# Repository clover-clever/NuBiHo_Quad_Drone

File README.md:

2025, first semester Microprocessor Quad Drone Project

Based on Arduino Uno R3 for control with PPM Signal

PPM for SPRacing R3

Self-made PCBs
  - 6V Regulator does not work well,(Burnt)(delete 6V Switching Regulator and use it)
  - LM1117 - 12V --> 5V(too big voltage difference, do not use for high load, or just do not use it)

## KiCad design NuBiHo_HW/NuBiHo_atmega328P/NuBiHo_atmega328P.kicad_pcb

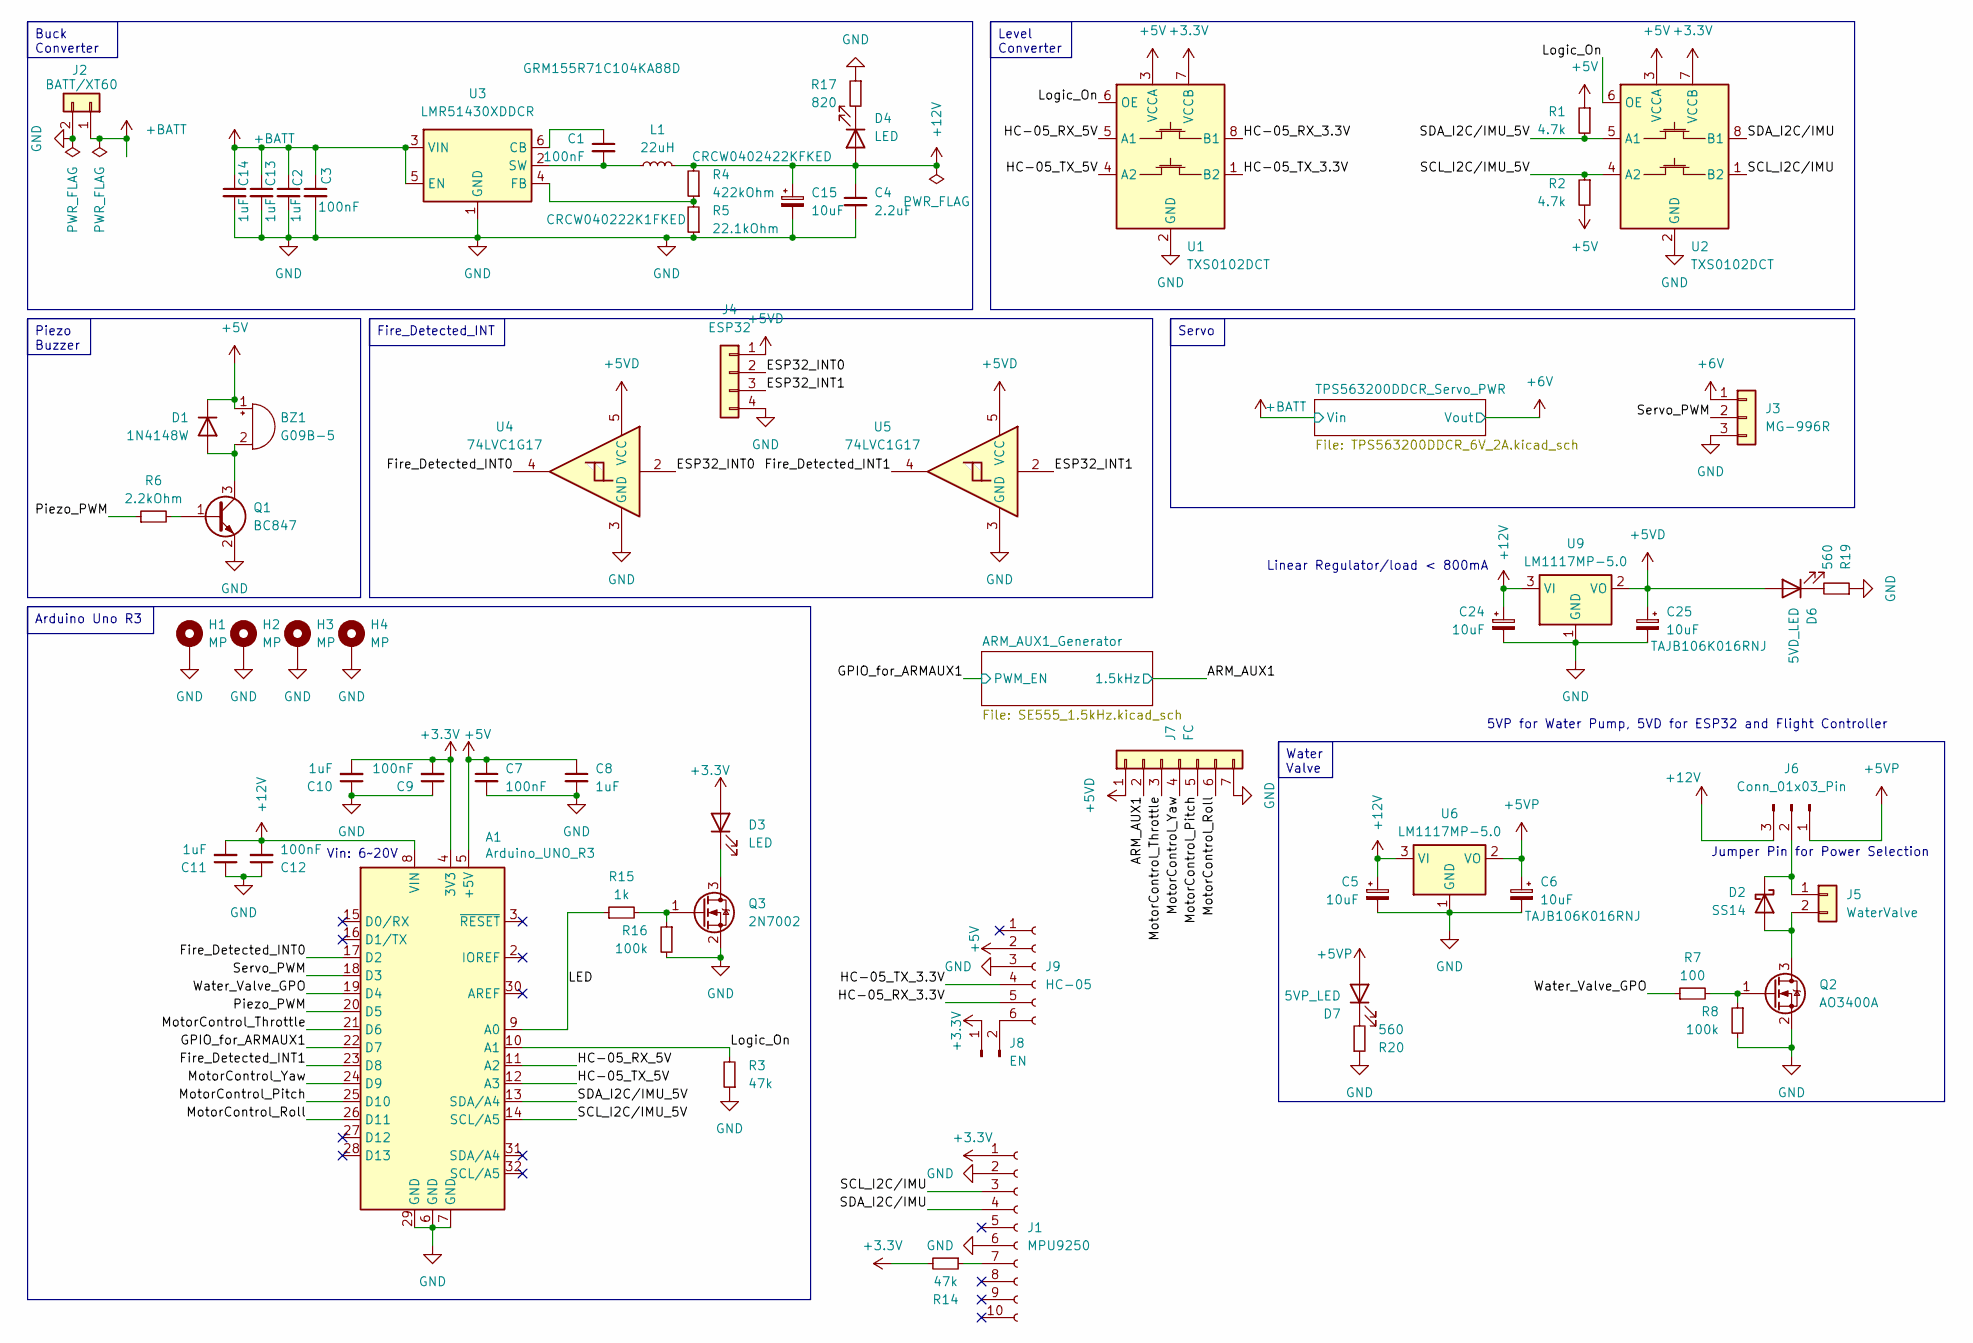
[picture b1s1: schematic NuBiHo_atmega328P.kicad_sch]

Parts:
A1: Arduino_UNO_R3
BZ1: G09B-5; [GEC] G09B-5
C1: 100nF; C_0402_1005Metric; Part No. GRM155R71C104KA88D
C2, C13, C14: 1uF; C_0603_1608Metric; Part No. GRM188R71E105KA12D
C3: 100nF; C_0805_2012Metric; Part No. GRM21BR71H104KA01L
C4: 2.2uF; C_0805_2012Metric; Part No. GRM21BR71C225KA12L
C5: 10uF; CP_EIA-3528-21_Kemet-B_Pad1.50x2.35mm_HandSolder
C6: 10uF; CP_EIA-3528-21_Kemet-B_Pad1.50x2.35mm_HandSolder; Part No. TAJB106K016RNJ
C7, C9, C12: 100nF; C_0402_1005Metric
C8, C10, C11: 1uF; C_0402_1005Metric
C15: 10uF; CP_EIA-6032-28_Kemet-C; Part No. 593D106X9025C2TE3
C24: 10uF; CP_EIA-3528-21_Kemet-B
C25: 10uF; CP_EIA-3528-21_Kemet-B; Part No. TAJB106K016RNJ
D1: 1N4148W; D_SOD-123
D2: SS14; D_SMA
D3, D4: LED; LED_0805_2012Metric
D6: 5VD_LED; LED_0805_2012Metric
D7: 5VP_LED; LED_0805_2012Metric
H1, H2, H3, H4: MP; MountingHole_3.2mm_M3_Pad_Via
J1: MPU9250; PinHeader_1x10_P2.54mm_Vertical
J2: BATT/XT60; AMASS_XT60-M_1x02_P7.20mm_Vertical
J3: MG-996R; Molex_SPOX_5267-03A_1x03_P2.50mm_Vertical
J4: ESP32; Molex_SPOX_5267-04A_1x04_P2.50mm_Vertical
J5: WaterValve; Molex_SPOX_5267-02A_1x02_P2.50mm_Vertical
J6: Conn_01x03_Pin; PinHeader_1x03_P2.54mm_Vertical
J7: FC; Molex_SPOX_5267-07A_1x07_P2.50mm_Vertical
J8: EN; PinHeader_1x02_P2.54mm_Vertical
J9: HC-05; PinHeader_1x06_P2.54mm_Vertical
L1: 22uH; INDPM172172X700N; Part No. IHLP6767GZER220M11
Q1: BC847; SOT-23
Q2: AO3400A; SOT-23
Q3: 2N7002; SOT-23
R1, R2: 4.7k; R_0402_1005Metric
R3, R14: 47k; R_0402_1005Metric
R4: 422kOhm; R_0603_1608Metric; Part No. CRCW0402422KFKED
R5: 22.1kOhm; R_0603_1608Metric; Part No. CRCW040222K1FKED
R6: 2.2kOhm; R_0402_1005Metric
R7: 100; R_0402_1005Metric
R8, R16: 100k; R_0402_1005Metric
R15: 1k; R_0402_1005Metric
R17: 820; R_0402_1005Metric
R19, R20: 560; R_0402_1005Metric
U1, U2: TXS0102DCT; SSOP-8_2.95x2.8mm_P0.65mm
U3: LMR51430XDDCR; SOT-23-6
U4, U5: 74LVC1G17; SOT-23-5
U6, U9: LM1117MP-5.0; SOT-223-3_TabPin2

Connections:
+3.3V: A1.4 (3V3), C9.2, C10.2, D3.2 (A), J1.1, J8.1, R14.2, U1.7 (VCCB), U2.7 (VCCB)
+5V: A1.5 (+5V), BZ1.1 (+), C7.1, C8.1, D1.1 (K), J9.2, R1.1, R2.2, U1.3 (VCCA), U2.3 (VCCA); also elsewhere on the board
+5VD: C25.1, D6.2 (A), J4.1, J7.1, U4.5 (VCC), U5.5 (VCC), U9.2 (VO)
+5VP: C6.1, D7.2 (A), J6.1, U6.2 (VO)
+6V: J3.1; also elsewhere on the board
+12V: A1.8 (VIN), C4.1, C5.1, C11.2, C12.2, C15.1, C24.1, D4.2 (A), J6.3, L1.2, R4.2, U6.3 (VI), U9.3 (VI)
+BATT: C2.1, C3.1, C13.1, C14.1, J2.1, U3.3 (VIN), U3.5 (EN); also elsewhere on the board
/ARM_AUX1: J7.2; also elsewhere on the board
/ESP32_INT0: J4.2, U4.2
/ESP32_INT1: J4.3, U5.2
/Fire_Detected_INT0: A1.17 (D2), U4.4
/Fire_Detected_INT1: A1.23 (D8), U5.4
/GPIO_for_ARMAUX1: A1.22 (D7); also elsewhere on the board
/HC-05_RX_3.3V: J9.5, U1.8 (B1)
/HC-05_RX_5V: A1.11 (A2), U1.5 (A1)
/HC-05_TX_3.3V: J9.4, U1.1 (B2)
/HC-05_TX_5V: A1.12 (A3), U1.4 (A2)
/LED: A1.9 (A0), R15.1
/Logic_On: A1.10 (A1), R3.2, U1.6 (OE), U2.6 (OE)
/MotorControl_Pitch: A1.25 (D10), J7.5
/MotorControl_Roll: A1.26 (D11), J7.6
/MotorControl_Throttle: A1.21 (D6), J7.3
/MotorControl_Yaw: A1.24 (D9), J7.4
/Piezo_PWM: A1.20 (D5), R6.1
/SCL_I2C/IMU: J1.3, U2.1 (B2)
/SCL_I2C/IMU_5V: A1.14 (SCL/A5), R2.1, U2.4 (A2)
/SDA_I2C/IMU: J1.4, U2.8 (B1)
/SDA_I2C/IMU_5V: A1.13 (SDA/A4), R1.2, U2.5 (A1)
/Servo_PWM: A1.18 (D3), J3.2
/Water_Valve_GPO: A1.19 (D4), R7.1
GND: A1.6 (GND), A1.7 (GND), A1.29 (GND), C2.2, C3.2, C4.2, C5.2, C6.2, C7.2, C8.2, C9.1, C10.1, C11.1, C12.1, C13.2, C14.2, C15.2, C24.2, C25.2, H1.1, H2.1, H3.1, H4.1, J1.2, J1.6, J2.2, J3.3, J4.4, J7.7, J9.3, Q1.2 (E), Q2.2 (S), Q3.2 (S), R3.1, R5.1, R8.2, R16.2, R17.1, R19.1, R20.1, U1.2 (GND), U2.2 (GND), U3.1 (GND), U4.3 (GND), U5.3 (GND), U6.1 (GND), U9.1 (GND); also elsewhere on the board
unnamed: BZ1.2 (-), D1.2 (A), Q1.3 (C)
unnamed: D2.2 (A), J5.2, Q2.3 (D)
unnamed: D2.1 (K), J5.1, J6.2
unnamed: D3.1 (K), Q3.3 (D)
unnamed: D4.1 (K), R17.2
unnamed: D6.1 (K), R19.2
unnamed: D7.1 (K), R20.2
unnamed: J1.7, R14.1
unnamed: J8.2, J9.6
unnamed: Q1.1 (B), R6.2
unnamed: Q2.1 (G), R7.2, R8.1
unnamed: Q3.1 (G), R15.2, R16.1
unnamed: C1.1, U3.6 (CB)
unnamed: R4.1, R5.2, U3.4 (FB)
unnamed: C1.2, L1.1, U3.2 (SW)

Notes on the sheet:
Vin: 6~20V
5VP for Water Pump, 5VD for ESP32 and Flight Controller
Linear Regulator/load < 800mA
Jumper Pin for Power Selection
Servo
Piezo Buzzer
Level Converter
Fire_Detected_INT
Arduino Uno R3
Water Valve
Buck Converter

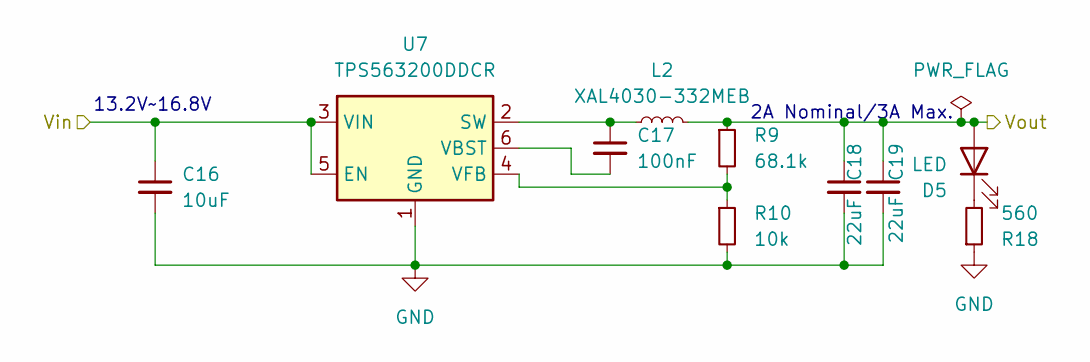
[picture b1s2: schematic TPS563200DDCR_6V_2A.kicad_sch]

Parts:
C16: 10uF; C_1206_3216Metric; Part No. GRM31CR61E106KA12L
C17: 100nF; C_0805_2012Metric; Part No. CC0805KRX7R9BB104
C18: 22uF; C_1206_3216Metric; Part No. GRM31CR71A226KE15L
C19: 22uF; C_1206_3216Metric
D5: LED; LED_0805_2012Metric
L2: XAL4030-332MEB; L_Coilcraft_XAL4030-XXX
R9: 68.1k; R_0603_1608Metric; Part No. RC0402FR-0768K1L
R10: 10k; R_0603_1608Metric; Part No. CRCW040210K0FKED
R18: 560; R_0402_1005Metric
U7: TPS563200DDCR; SOT-23-6

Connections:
+6V: C18.1, C19.1, D5.2 (A), L2.2, R9.1; also elsewhere on the board
+BATT: C16.1, U7.3 (VIN), U7.5 (EN); also elsewhere on the board
GND: C16.2, C18.2, C19.2, R10.2, R18.1, U7.1 (GND); also elsewhere on the board
unnamed: D5.1 (K), R18.2
unnamed: C17.1, L2.1, U7.2 (SW)
unnamed: C17.2, U7.6 (VBST)
unnamed: R9.2, R10.1, U7.4 (VFB)

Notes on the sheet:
2A Nominal/3A Max.
13.2V~16.8V

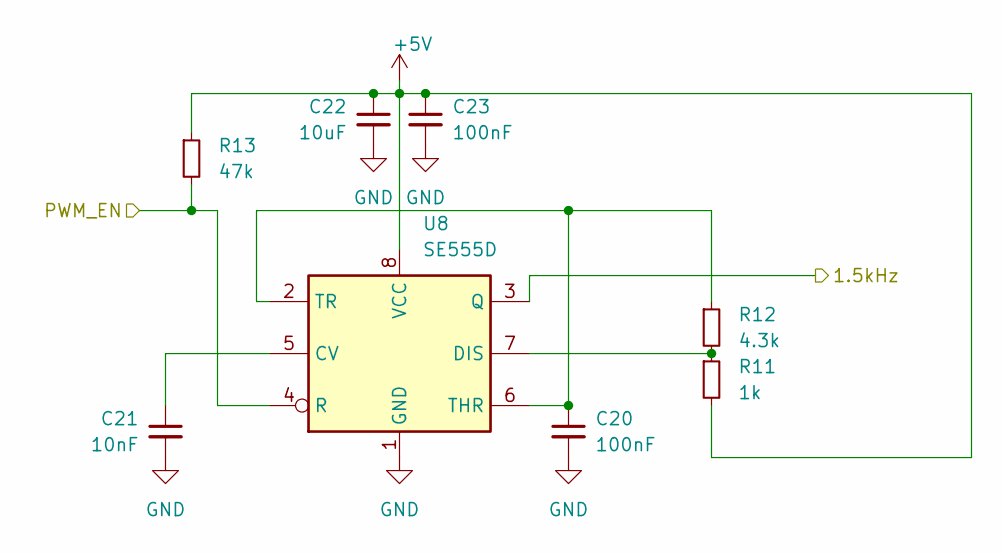
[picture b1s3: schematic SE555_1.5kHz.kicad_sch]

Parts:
C20: 100nF; C_1206_3216Metric
C21: 10nF; C_0603_1608Metric
C22: 10uF; C_0402_1005Metric
C23: 100nF; C_0402_1005Metric
R11: 1k; R_0402_1005Metric
R12: 4.3k; R_0402_1005Metric
R13: 47k; R_0402_1005Metric
U8: SE555D; SOIC-8_3.9x4.9mm_P1.27mm

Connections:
+5V: C22.1, C23.1, R11.2, R13.1, U8.8 (VCC); also elsewhere on the board
/ARM_AUX1: U8.3 (Q); also elsewhere on the board
/GPIO_for_ARMAUX1: R13.2, U8.4 (R); also elsewhere on the board
GND: C20.2, C21.2, C22.2, C23.2, U8.1 (GND); also elsewhere on the board
unnamed: C21.1, U8.5 (CV)
unnamed: R11.1, R12.2, U8.7 (DIS)
unnamed: C20.1, R12.1, U8.2 (TR), U8.6 (THR)

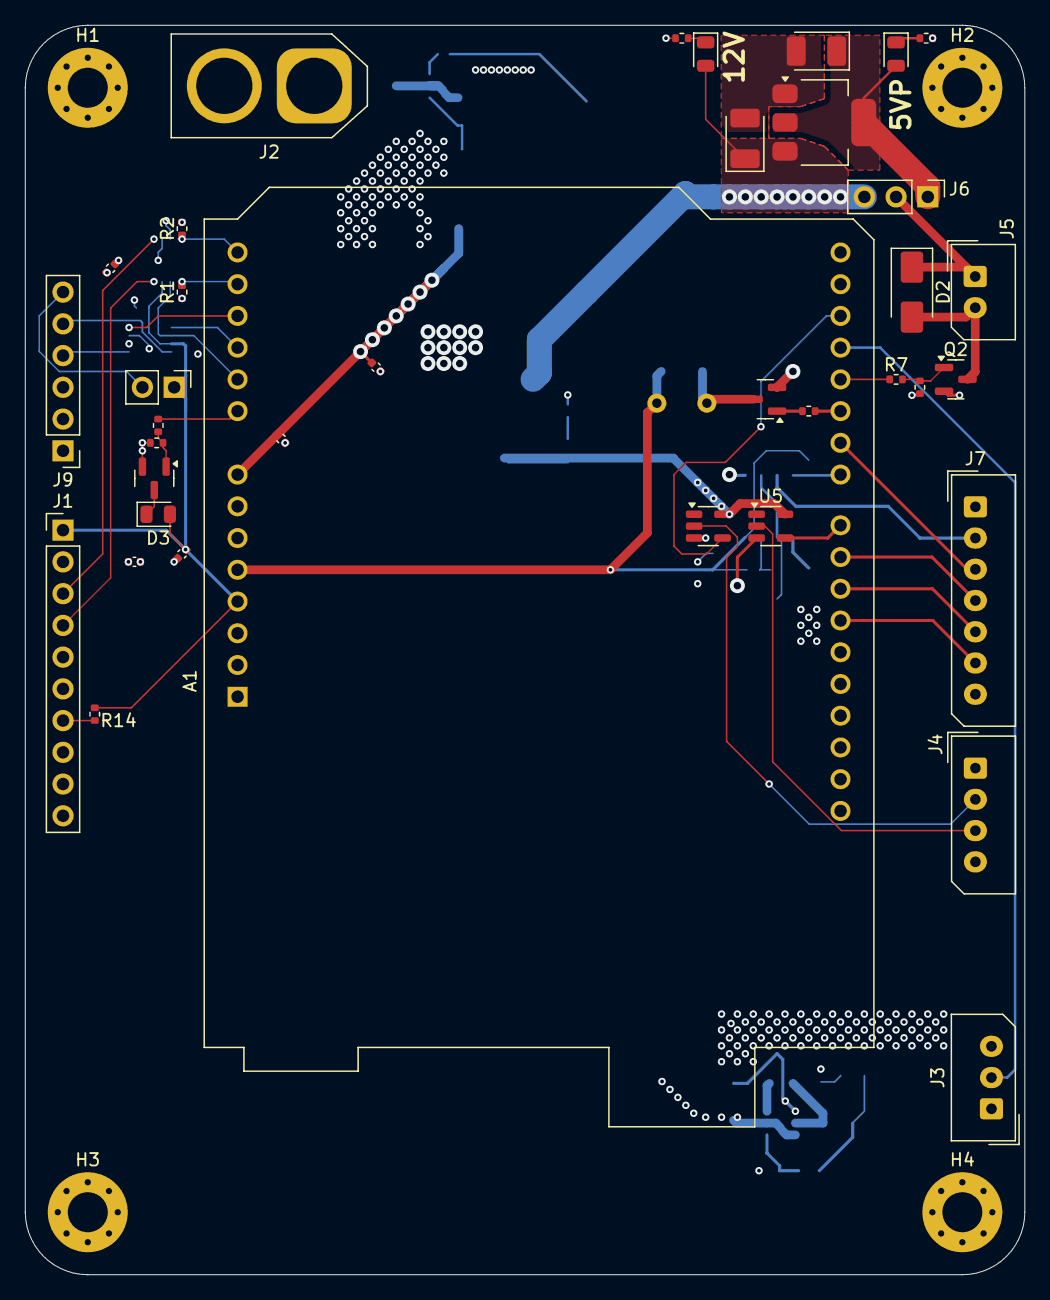
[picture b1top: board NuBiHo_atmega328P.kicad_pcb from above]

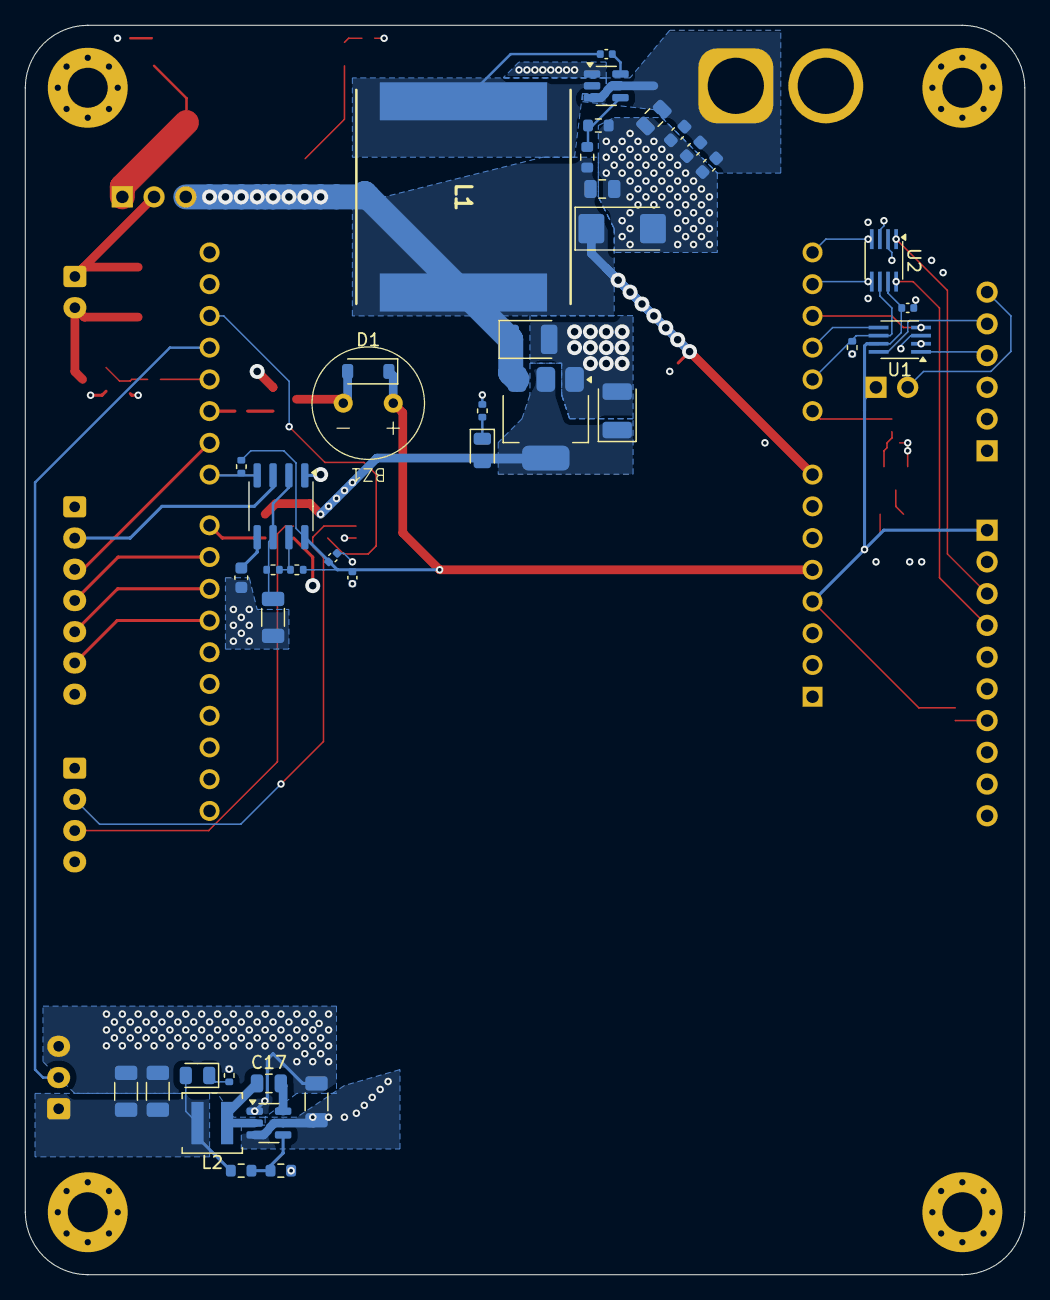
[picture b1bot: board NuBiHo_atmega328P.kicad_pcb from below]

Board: 4 copper layers, 80.0 x 100.0 mm, 81 parts (40 on the bottom side), 53 nets.

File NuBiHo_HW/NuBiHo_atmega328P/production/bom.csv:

Designator,Footprint,Quantity,Value,LCSC Part #
A1,Arduino_UNO_R3,1,Arduino_UNO_R3,
BZ1,[GEC] G09B-5,1,G09B-5,
"C1, C12, C23, C7, C9",0402,5,100nF,
"C10, C11, C8",0402,3,1uF,
"C13, C14, C2",0603,3,1uF,
C15,CP_EIA-6032-28_Kemet-C,1,10uF,
C16,1206,1,10uF,
"C17, C3",0805,2,100nF,
"C18, C19",1206,2,22uF,
C20,1206,1,100nF,
C21,0603,1,10nF,
C22,0402,1,10uF,
"C24, C25",CP_EIA-3528-21_Kemet-B,2,10uF,
C4,0805,1,2.2uF,
"C5, C6",CP_EIA-3528-21_Kemet-B_Pad1.50x2.35mm_HandSolder,2,10uF,
D1,D_SOD-123,1,1N4148W,
D2,D_SMA,1,SS14,
"D3, D4, D5",0805,3,LED,
D6,0805,1,5VD_LED,
D7,0805,1,5VP_LED,
J1,PinHeader_1x10_P2.54mm_Vertical,1,MPU9250,
J2,AMASS_XT60-M_1x02_P7.20mm_Vertical,1,BATT/XT60,
J3,Molex_SPOX_5267-03A_1x03_P2.50mm_Vertical,1,MG-996R,
J4,Molex_SPOX_5267-04A_1x04_P2.50mm_Vertical,1,ESP32,
J5,Molex_SPOX_5267-02A_1x02_P2.50mm_Vertical,1,WaterValve,
J6,PinHeader_1x03_P2.54mm_Vertical,1,Conn_01x03_Pin,
J7,Molex_SPOX_5267-07A_1x07_P2.50mm_Vertical,1,FC,
J8,PinHeader_1x02_P2.54mm_Vertical,1,EN,
J9,PinHeader_1x06_P2.54mm_Vertical,1,HC-05,
L1,INDPM172172X700N,1,22uH,
L2,L_Coilcraft_XAL4030-XXX,1,XAL4030-332MEB,
Q1,SOT-23,1,BC847,
Q2,SOT-23,1,AO3400A,
Q3,SOT-23,1,2N7002,
"R1, R2",0402,2,4.7k,
R10,0603,1,10k,
"R11, R15",0402,2,1k,
R12,0402,1,4.3k,
"R13, R14, R3",0402,3,47k,
"R16, R8",0402,2,100k,
R17,0402,1,820,
"R18, R19, R20",0402,3,560,
R4,0603,1,422kOhm,
R5,0603,1,22.1kOhm,
R6,0402,1,2.2kOhm,
R7,0402,1,100,
R9,0603,1,68.1k,
"U1, U2",SSOP-8_2.95x2.8mm_P0.65mm,2,TXS0102DCT,
U3,SOT-23-6,1,LMR51430XDDCR,
"U4, U5",SOT-23-5,2,74LVC1G17,
"U6, U9",SOT-223-3_TabPin2,2,LM1117MP-5.0,
U7,SOT-23-6,1,TPS563200DDCR,
U8,SOIC-8_3.9x4.9mm_P1.27mm,1,SE555D,

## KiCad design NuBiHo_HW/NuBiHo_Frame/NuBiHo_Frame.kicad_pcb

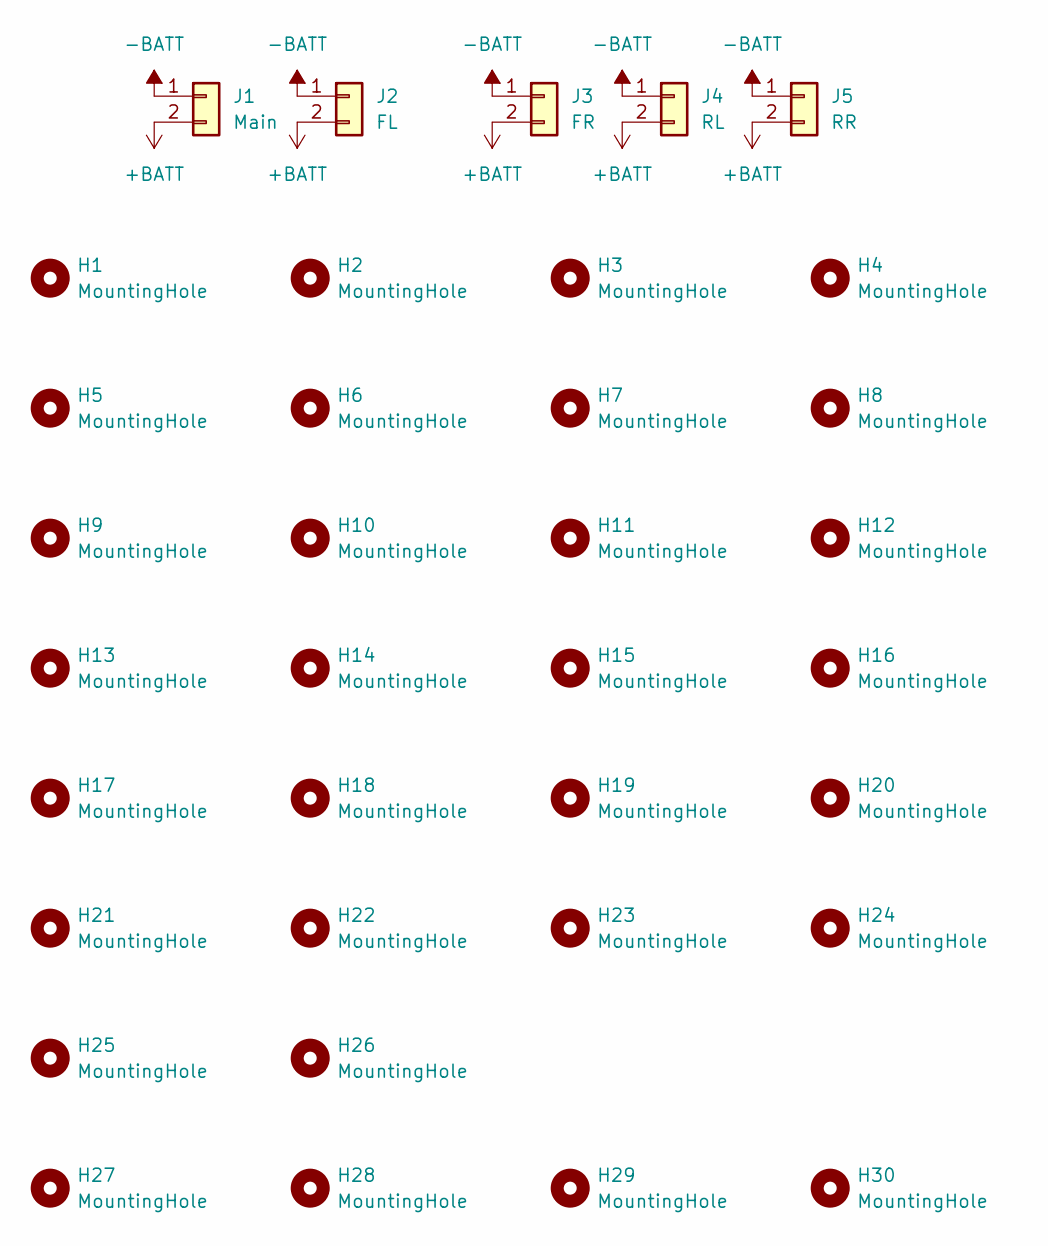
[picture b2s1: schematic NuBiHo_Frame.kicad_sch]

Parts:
H1, H2, H3, H4, H5, H6, H7, H8, H9, H10, H11, H12, H13, H14, H15, H16, H17, H18, H19, H20, H21, H22, H23, H24, H25, H26, H27, H28, H29, H30: MountingHole; MountingHole_3.2mm_M3_DIN965_Pad
J1: Main; AMASS_XT60-M_1x02_P7.20mm_Vertical
J2: FL; AMASS_XT60-M_1x02_P7.20mm_Vertical
J3: FR; AMASS_XT60-M_1x02_P7.20mm_Vertical
J4: RL; AMASS_XT60-M_1x02_P7.20mm_Vertical
J5: RR; AMASS_XT60-M_1x02_P7.20mm_Vertical

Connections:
+BATT: J1.2, J2.2, J3.2, J4.2, J5.2
-BATT: J1.1, J2.1, J3.1, J4.1, J5.1

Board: 2 copper layers, 35 parts (0 on the bottom side), 2 nets, no tracks yet.

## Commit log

2025-06-20 2025_Microprocessor_Drone_Project_Initial Commit
2025-06-20 commit practice
2025-06-20 Read Me.md
